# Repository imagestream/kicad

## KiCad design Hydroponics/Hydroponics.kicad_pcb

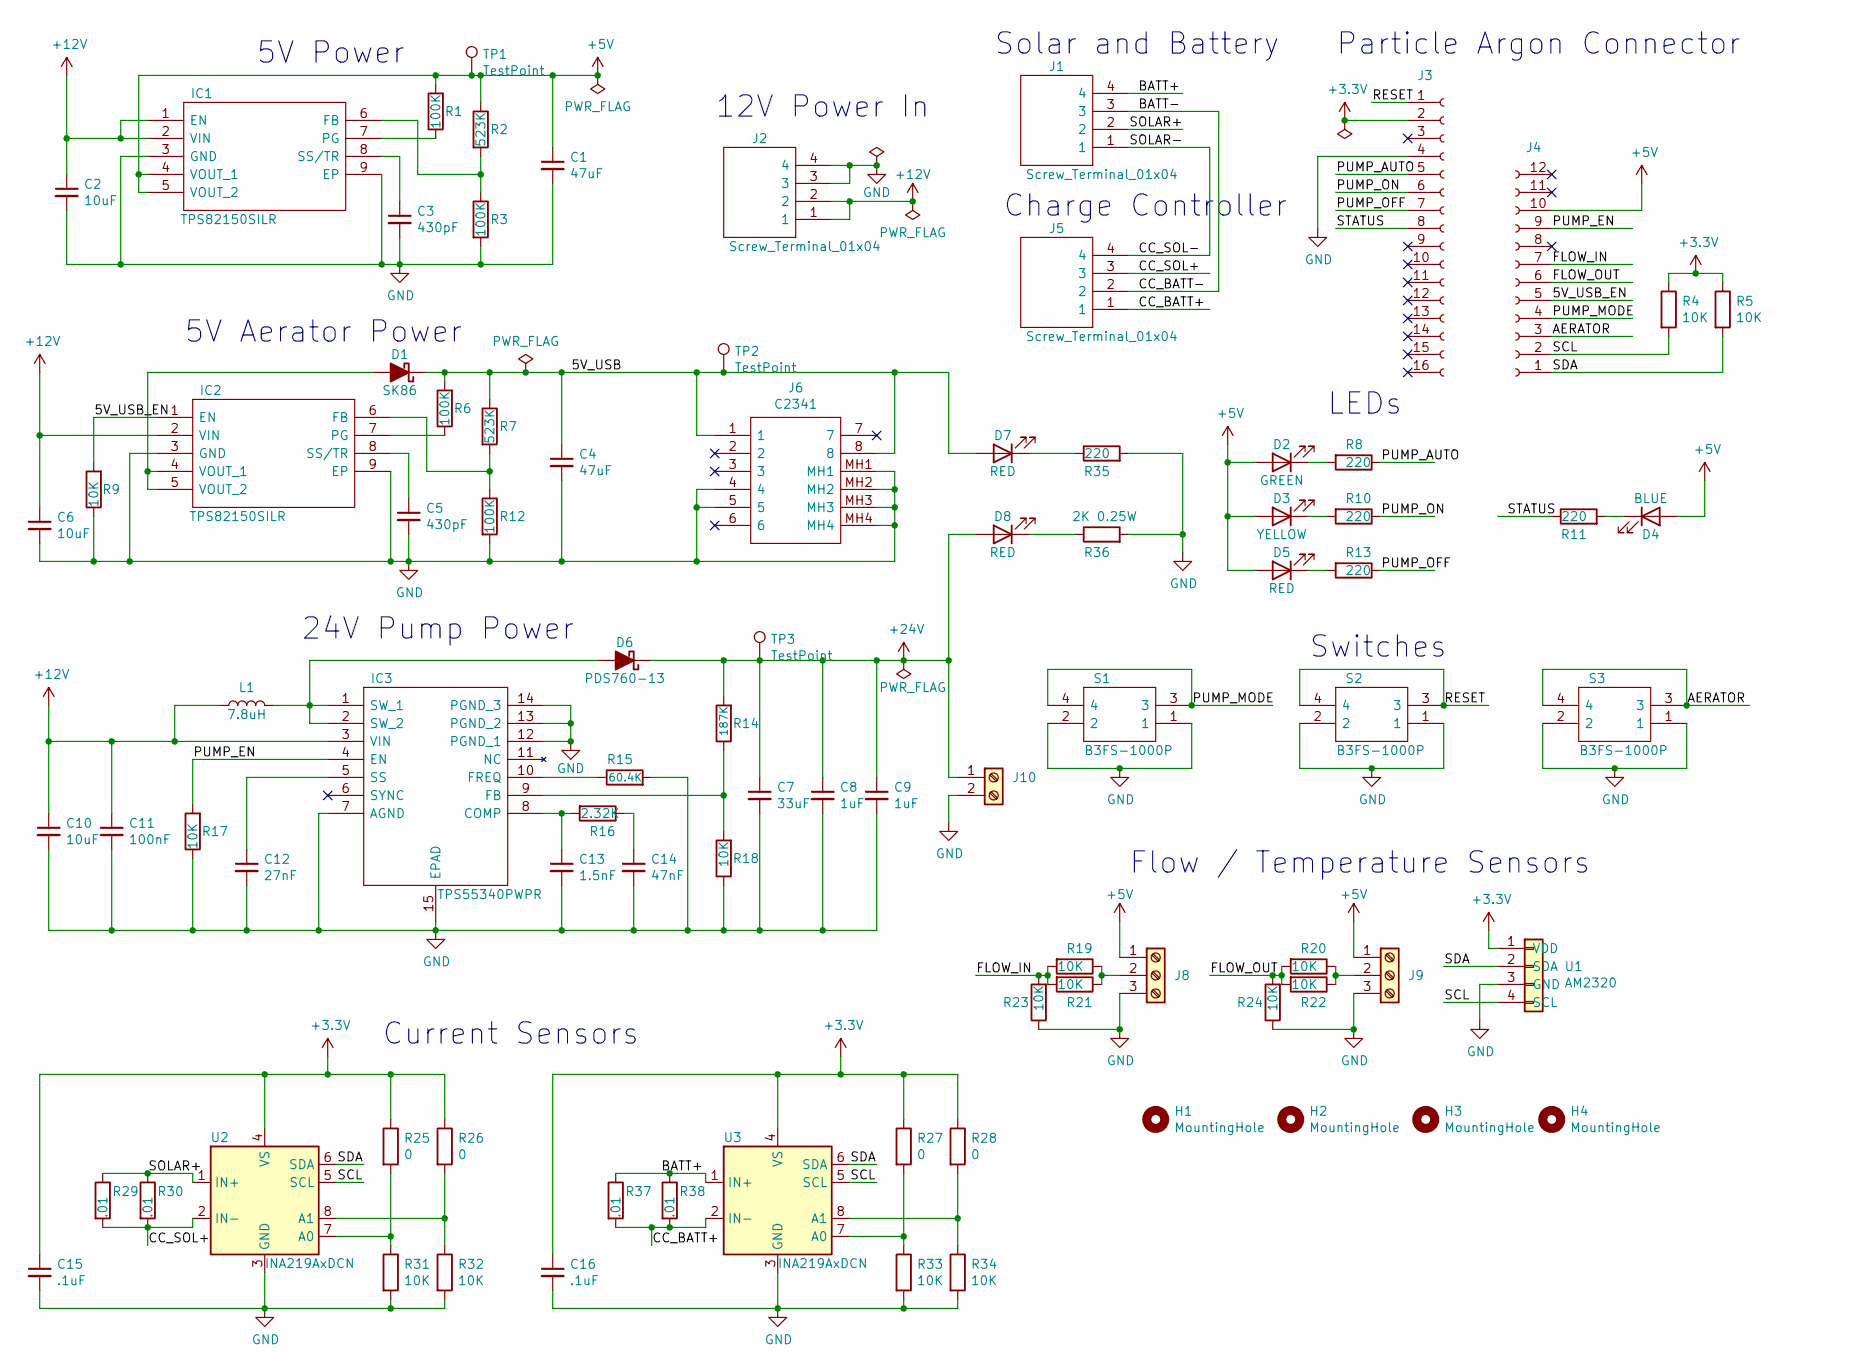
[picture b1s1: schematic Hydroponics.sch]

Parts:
C1, C4: 47uF; C_1206_3216Metric; MPN CL31A476MQHNNNE
C2, C6, C10: 10uF; C_1206_3216Metric; MPN CL31A106KOHNNNE
C3, C5: 430pF; C_0603_1608Metric; MPN 0603B431K500NT
C7: 33uF; C_Elec_6.3x7.7; MPN EEHZA1H330XP
C8, C9: 1uF; C_0805_2012Metric; MPN CL21B105KBFNNNE
C11: 100nF; C_0805_2012Metric; MPN 0805B104K500NT
C12: 27nF; C_0603_1608Metric; MPN CL10B273KB8NNNC
C13: 1.5nF; C_0805_2012Metric; MPN 0805B152K500NT
C14: 47nF; C_0805_2012Metric; MPN CL21B473KBANNNC
C15, C16: .1uF; C_0603_1608Metric; MPN 0603B104K500NT
D1: SK86; D_SMC; MPN SK86
D2: GREEN; LED_0805_2012Metric; MPN LTST-C171KGKT
D3: YELLOW; LED_0805_2012Metric; MPN LTST-C170YKT
D4: BLUE; LED_0805_2012Metric; MPN LTST-C171TBKT
D5, D7, D8: RED; LED_0805_2012Metric; MPN LTST-C170KRKT
D6: PDS760-13; D_PowerDI-5; MPN PDS760-13
H1, H2, H3, H4: MountingHole; MountingHole_3mm
IC1, IC2: TPS82150SILR; TPS82130SILT; Manufacturer_Part_Number TPS82150SILR; Mouser Part Number 595-TPS82150SILR
IC3: TPS55340PWPR; SOP65P640X120-15N; Manufacturer_Part_Number TPS55340PWPR; Mouser Part Number 595-TPS55340PWPR
J1, J2, J5: Screw_Terminal_01x04; 691313410004; MPN 1766259
J3: Conn_01x16_Female; PinSocket_1x16_P2.54mm_Vertical; MPN C66987
J4: Conn_01x12_Female; PinSocket_1x12_P2.54mm_Vertical; MPN A2541HWV-12P
J6: C2341; Manufacturer_Part_Number C2341
J8, J9: 282834-3; TerminalBlock_TE_282834-3_1x03_P2.54mm_Horizontal; MPN 282834-3
J10: 282834-2; TerminalBlock_TE_282834-2_1x02_P2.54mm_Horizontal; MPN 282834-2
L1: 7.8uH; L_TDK_RLF12560; MPN RLF12560T-7R8N8R2
R1, R3, R6, R12: 100K; R_0603_1608Metric; MPN CR0603-FX-1003ELF
R2, R7: 523K; R_0603_1608Metric; MPN CR0603-FX-5233ELF
R4, R5, R9, R17, R18, R19, R20, R21, R22, R23, R24, R31, R32, R33, R34: 10K; R_0603_1608Metric; MPN RS-03K103JT
R8, R10, R11, R13, R35: 220; R_0603_1608Metric; MPN 0603WAF2200T5E
R14: 187K; R_0603_1608Metric; MPN 0603WAF1873T5E
R15: 60.4K; R_0603_1608Metric; MPN 0603WAF6042T5E
R16: 2.32K; R_0603_1608Metric; MPN 0603WAF2321T5E
R25, R26, R27, R28: 0; R_0603_1608Metric; MPN 0603WAF0000T5E
R29, R37: .01; R_Shunt_Vishay_WSR2_WSR3; MPN WSR3R0100FEA
R30, R38: .01; R_2512_6332Metric; MPN 25121WJ010LT4E
R36: 2K 0.25W; R_0603_1608Metric; MPN ERJPA3J202V
S1, S2, S3: B3FS-1000P; Manufacturer_Part_Number B3FS-1000P; Mouser Part Number 653-B3FS-1000P
TP1, TP2, TP3: TestPoint; TestPoint_Plated_Hole_D2.0mm
U1: AM2320; PinHeader_1x04_P2.54mm_Vertical; MPN AM2320
U2, U3: INA219AxDCN; SOT-23-8; MPN INA219AIDCNR

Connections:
+3V3: C15.1, C16.1, J3.2, R4.1, R5.1, R25.1, R26.1, R27.1, R28.1, U1.1 (VDD), U2.4 (VS), U3.4 (VS)
+5V: C1.1, D2.2 (A), D3.2 (A), D4.2 (A), D5.2 (A), IC1.4 (VOUT_1), IC1.5 (VOUT_2), J4.10, J8.1, J9.1, R1.2, R2.1, TP1.1
+12V: C2.1, C6.1, C10.1, C11.1, IC1.1 (EN), IC1.2 (VIN), IC2.2 (VIN), IC3.3 (VIN), J2.1, J2.2, L1.1
+24V: C7.1, C8.1, C9.1, D6.1 (K), D8.2 (A), J10.1, R14.2, TP3.1
/5V_USB: C4.1, D1.1 (K), D7.2 (A), J6.1, J6.8, R6.2, R7.1, TP2.1
/5V_USB_EN: IC2.1 (EN), J4.5, R9.2
/AERATOR: J4.3, S3.3, S3.4
/BATT+: J1.4, R37.1, R38.1, U3.1 (IN+)
/BATT-: J1.3, J5.2
/CC_BATT+: J5.1, R37.2, R38.2, U3.2 (IN-)
/CC_SOL+: J5.3, R29.2, R30.2, U2.2 (IN-)
/CC_SOL-: J1.1, J5.4
/FLOW_IN: J4.7, R19.2, R21.2, R23.2
/FLOW_OUT: J4.6, R20.2, R22.2, R24.2
/PUMP_AUTO: J3.5, R8.1
/PUMP_EN: IC3.4 (EN), J4.9, R17.2
/PUMP_MODE: J4.4, S1.3, S1.4
/PUMP_OFF: J3.7, R13.1
/PUMP_ON: J3.6, R10.1
/RESET: J3.1, S2.3, S2.4
/SCL: J4.2, R4.2, U1.4 (SCL), U2.5 (SCL), U3.5 (SCL)
/SDA: J4.1, R5.2, U1.2 (SDA), U2.6 (SDA), U3.6 (SDA)
/SOLAR+: J1.2, R29.1, R30.1, U2.1 (IN+)
/STATUS: J3.8, R11.1
GND: C1.2, C2.2, C3.2, C4.2, C5.2, C6.2, C7.2, C8.2, C9.2, C10.2, C11.2, C12.2, C13.2, C14.2, C15.2, C16.2, IC1.3 (GND), IC1.9 (EP), IC2.3 (GND), IC2.9 (EP), IC3.7 (AGND), IC3.12 (PGND_1), IC3.13 (PGND_2), IC3.14 (PGND_3), IC3.15 (EPAD), J2.3, J2.4, J3.4, J6.4, J6.5, J6.MH1, J6.MH2, J6.MH3, J6.MH4, J8.3, J9.3, J10.2, R3.2, R9.1, R12.2, R15.2, R17.1, R18.1, R23.1, R24.1, R31.2, R32.2, R33.2, R34.2, R35.2, R36.2, S1.1, S1.2, S2.1, S2.2, S3.1, S3.2, U1.3 (GND), U2.3 (GND), U3.3 (GND)
unnamed: C3.1, IC1.8 (SS/TR)
unnamed: C5.1, IC2.8 (SS/TR)
unnamed: C12.1, IC3.5 (SS)
unnamed: C13.1, IC3.8 (COMP), R16.2
unnamed: C14.1, R16.1
unnamed: D1.2 (A), IC2.4 (VOUT_1), IC2.5 (VOUT_2)
unnamed: D2.1 (K), R8.2
unnamed: D3.1 (K), R10.2
unnamed: D4.1 (K), R11.2
unnamed: D5.1 (K), R13.2
unnamed: D6.2 (A), IC3.1 (SW_1), IC3.2 (SW_2), L1.2
unnamed: D7.1 (K), R35.1
unnamed: D8.1 (K), R36.1
unnamed: IC1.6 (FB), R2.2, R3.1
unnamed: IC1.7 (PG), R1.1
unnamed: IC2.6 (FB), R7.2, R12.1
unnamed: IC2.7 (PG), R6.1
unnamed: IC3.9 (FB), R14.1, R18.2
unnamed: IC3.10 (FREQ), R15.1
unnamed: J8.2, R19.1, R21.1
unnamed: J9.2, R20.1, R22.1
unnamed: R25.2, R31.1, U2.7 (A0)
unnamed: R26.2, R32.1, U2.8 (A1)
unnamed: R27.2, R33.1, U3.7 (A0)
unnamed: R28.2, R34.1, U3.8 (A1)

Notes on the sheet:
12V Power In
Solar and Battery
Charge Controller
Current Sensors
24V Pump Power
5V Aerator Power
5V Power
Particle Argon Connector
Switches
LEDs
Flow / Temperature Sensors

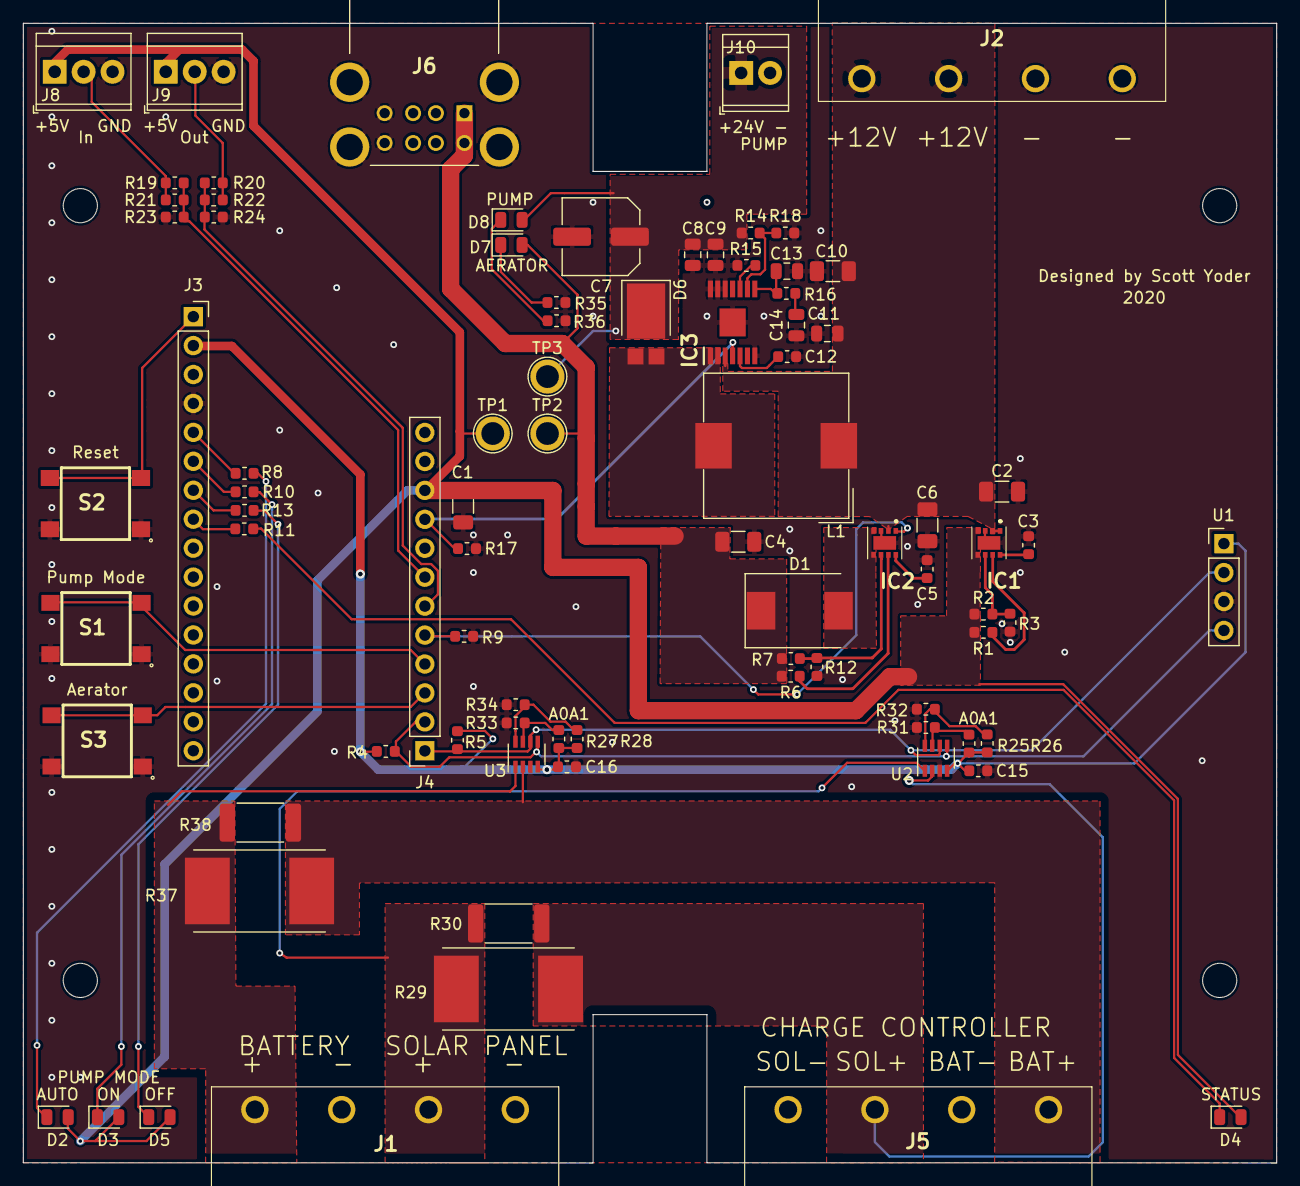
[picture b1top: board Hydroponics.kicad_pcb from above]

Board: 2 copper layers, 110.0 x 100.0 mm, 88 parts (0 on the bottom side), 50 nets.

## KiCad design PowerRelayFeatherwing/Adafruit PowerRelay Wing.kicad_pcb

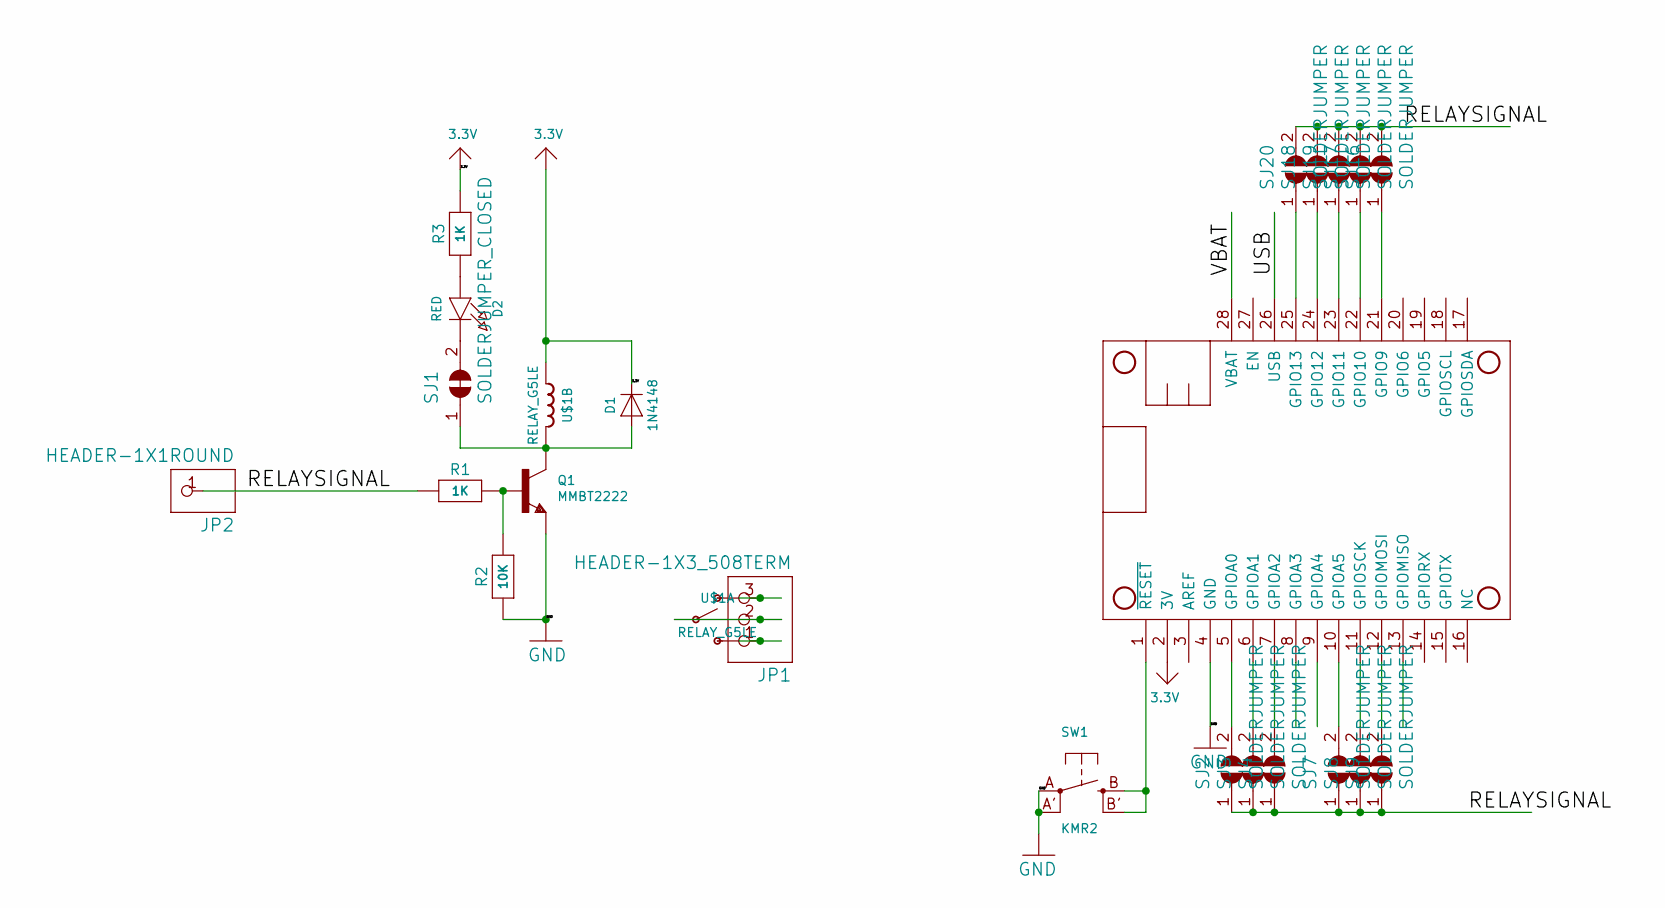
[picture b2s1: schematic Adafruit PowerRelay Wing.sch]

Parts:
D1: 1N4148; SOD-323
D2: RED; CHIPLED_0805_NOOUTLINE
JP1: HEADER-1X3_508TERM; TERMBLOCK_1X3_5.08MM
JP2: HEADER-1X1ROUND; 1X01_ROUND
MS2: FEATHERWING
Q1: MMBT2222; SOT23-R
R1, R3: 1K; 0805-NO
R2: 10K; 0805-NO
SJ1: SOLDERJUMPER_CLOSED; SOLDERJUMPER_CLOSEDWIRE
SJ2, SJ3, SJ4, SJ7, SJ8, SJ9, SJ16, SJ17, SJ18, SJ19, SJ20: SOLDERJUMPER; SOLDERJUMPER_ARROW_NOPASTE
SW1: KMR2; BTN_KMR2_4.6X2.8
U$1: RELAY_G5LE; RELAY_G5LE-1

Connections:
3.3V: D1.C, MS2.2 (3V), R3.2, U$1.2 (1)
/RELAYSIGNAL: JP2.1, R1.1, SJ2.1, SJ3.1, SJ4.1, SJ7.1, SJ8.1, SJ9.1, SJ16.2, SJ17.2, SJ18.2, SJ19.2, SJ20.2
/USB: MS2.26 (USB)
/VBAT: MS2.28 (VBAT)
GND: MS2.4 (GND), Q1.2 (E), R2.1, SW1.A, SW1.A' (P1)
unnamed: D1.A, Q1.3 (C), SJ1.1, U$1.5 (2)
unnamed: D2.A, R3.1
unnamed: D2.C, SJ1.2
unnamed: JP1.1, U$1.4 (S)
unnamed: JP1.2, U$1.1
unnamed: JP1.3, U$1.3 (O)
unnamed: MS2.1 (~RESET), SW1.B (S), SW1.B' (S1)
unnamed: MS2.5 (GPIOA0), SJ2.2
unnamed: MS2.6 (GPIOA1), SJ3.2
unnamed: MS2.7 (GPIOA2), SJ4.2
unnamed: MS2.10 (GPIOA5), SJ7.2
unnamed: MS2.11 (GPIOSCK), SJ8.2
unnamed: MS2.12 (GPIOMOSI), SJ9.2
unnamed: MS2.21 (GPIO9), SJ16.1
unnamed: MS2.22 (GPIO10), SJ17.1
unnamed: MS2.23 (GPIO11), SJ19.1
unnamed: MS2.24 (GPIO12), SJ18.1
unnamed: MS2.25 (GPIO13), SJ20.1
unnamed: Q1.1 (B), R1.2, R2.2

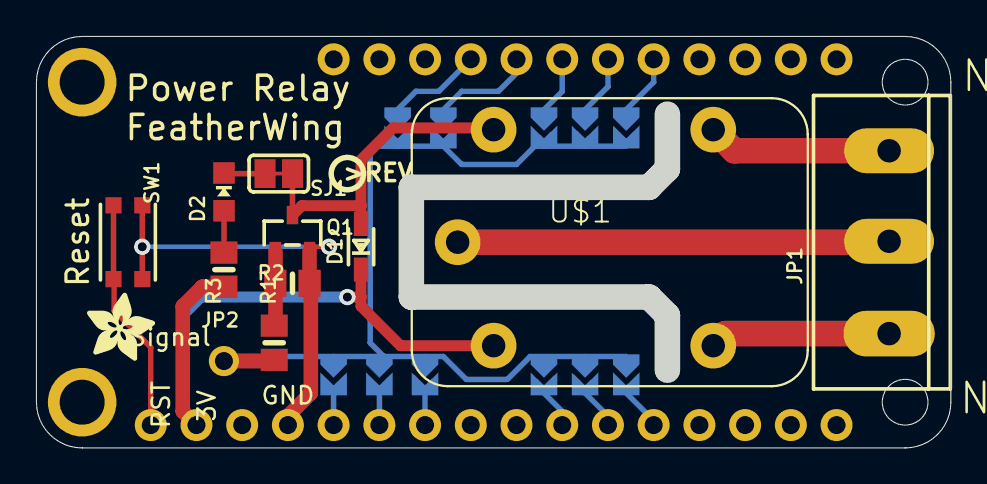
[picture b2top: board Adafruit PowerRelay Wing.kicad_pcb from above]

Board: 2 copper layers, 50.8 x 22.9 mm, 26 parts (0 on the bottom side), 22 nets.

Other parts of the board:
U$5: PCBFEAT-REV-040
U$6: ADAFRUIT_3.5MM
U$7: FEATHERLOGO_MED
